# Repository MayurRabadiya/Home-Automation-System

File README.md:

# Home Automation System
## What is Home Automation?
Home automation, often referred to as smart home technology, involves the automation of household activities through various control systems. This includes the monitoring and control of home attributes such as lighting, climate, entertainment systems, and appliances. Additionally, home automation encompasses security features like access control and alarm systems. When connected to the Internet, these devices become integral components of the Internet of Things (IoT).

## Project Aim
The objective of our Smart Module is to provide a comprehensive solution for controlling home electronic appliances using a smartphone, touch control, IR remote, and voice assistants like Alexa and Google Assistant.

## Modes of Operation
1. Touch Control: Utilizes a Cypress capacitive touch sensor to detect user touch inputs and respond based on the previous state of the relay.

2. Voice Command: Voice commands are facilitated through Alexa, which publishes MQTT messages. The ESP8266 module subscribes to these topics to receive the messages. Communication between the Cypress chip and ESP8266 occurs via I2C, enabling the system to react appropriately.

3. IR Remote: The ESP8266 decodes input from an IR remote and sends commands to the Cypress chip via I2C communication. The Cypress chip processes these commands to control the relays.

4. Smartphone: A smartphone app publishes MQTT messages that the ESP8266 module subscribes to. These messages are communicated to the Cypress chip through I2C, enabling the system to control the relays based on the received commands.

This project demonstrates the integration of various modern technologies to create a versatile and user-friendly home automation system.

## Images
Touch pad top side           |  Touch pad bottom side
:-------------------------:|:-------------------------:
  |  

Power base top side           |  Power base bottom side
:-------------------------:|:-------------------------:
  |  

Front Cover      
| :-------------------------:|
|   |

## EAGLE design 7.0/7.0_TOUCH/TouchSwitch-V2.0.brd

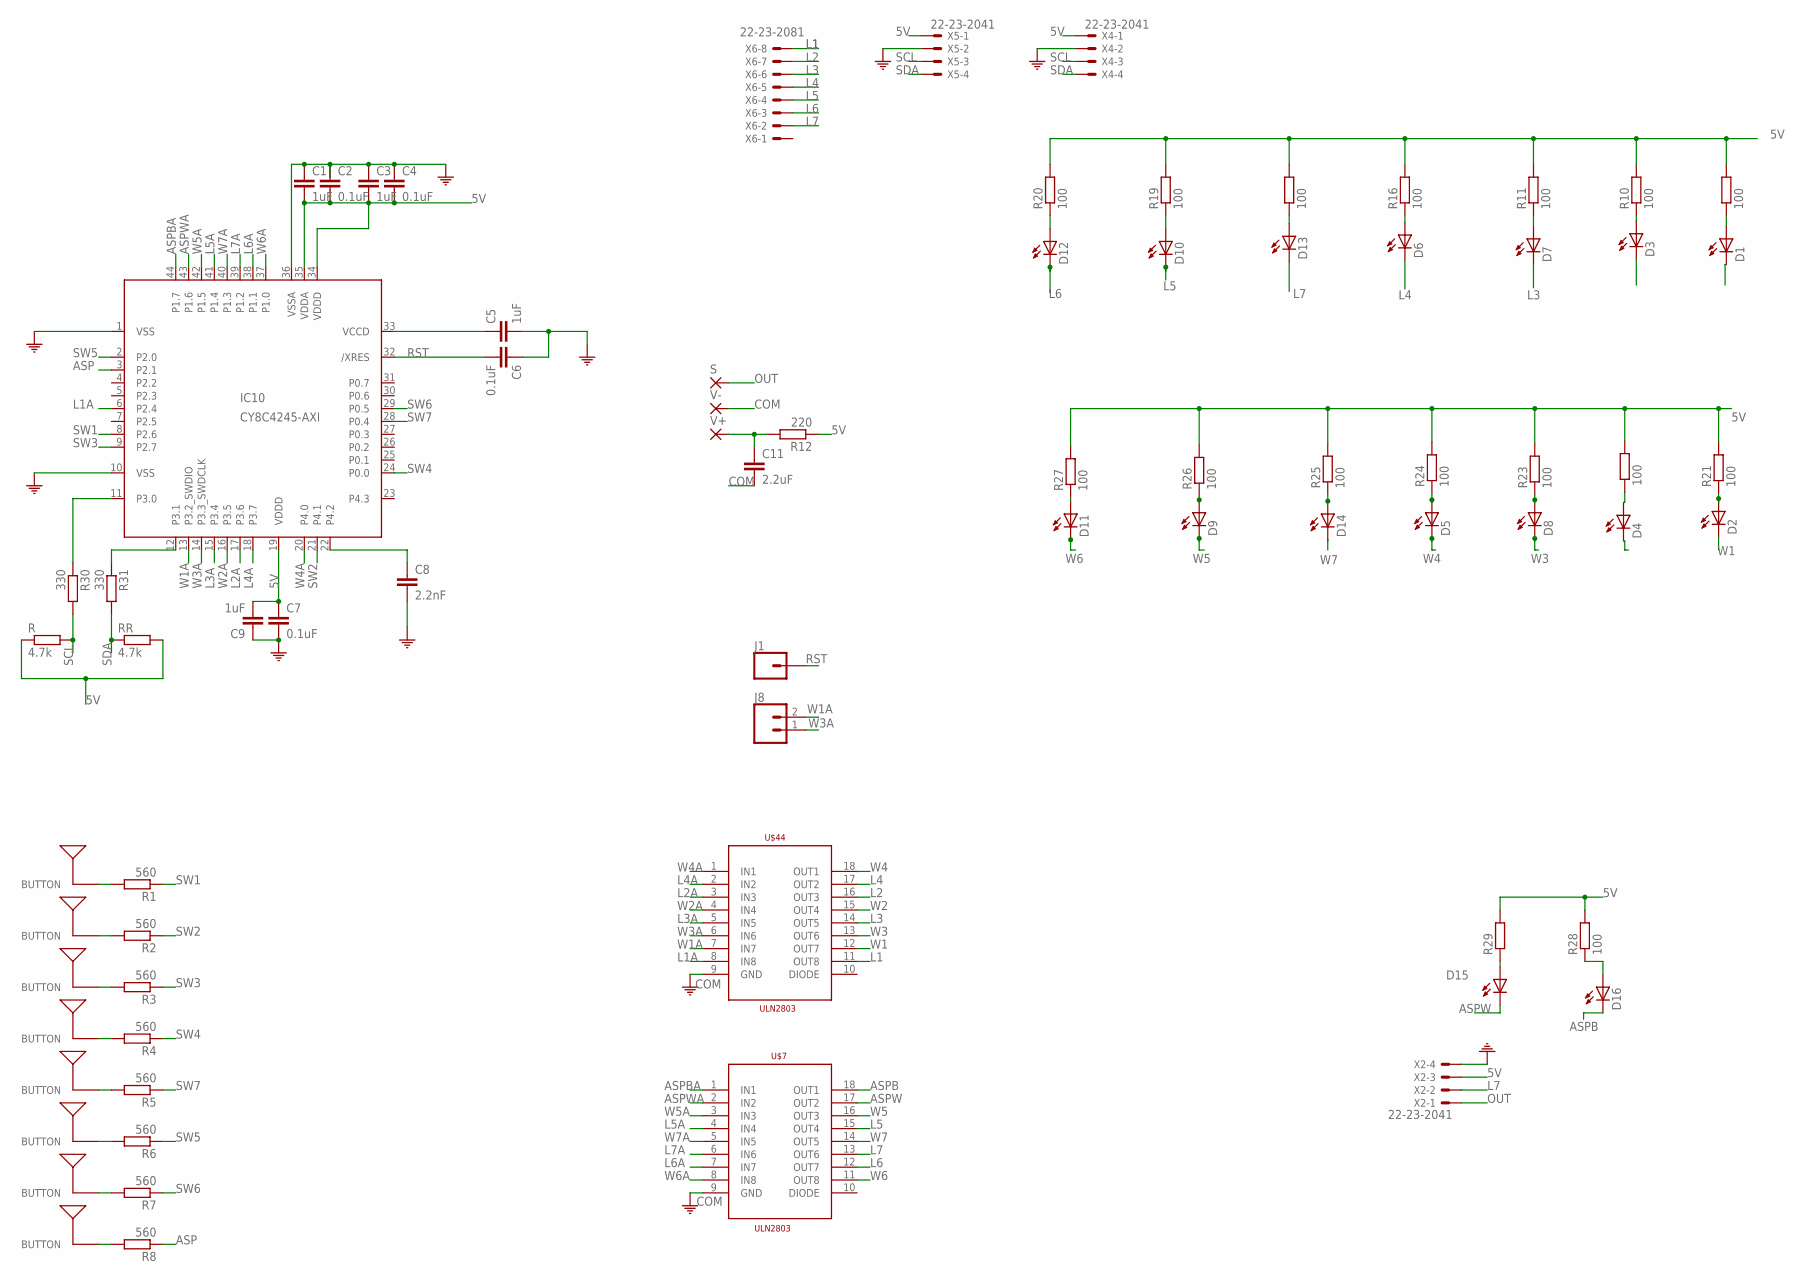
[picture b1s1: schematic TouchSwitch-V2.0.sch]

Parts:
B1, B2, B3, B4, B5, B6, B7, B8: BUTTON_PASSIVE12MM; BUTTON_PASSIVE_12MM
C1, C3, C5, C9: 1uF; C1206
C2, C4, C6, C7: 0.1uF; C1206
C8: 2.2nF; C1206
C11: 2.2uF; C1206
D1, D2, D3, D4, D5, D6, D7, D8, D9, D10, D11, D12, D13, D14, D15, D16: LEDCHIPLED_1206; CHIPLED_1206
IC10: CY8C4245-AXI; 44-TQFP-0.8
J1: CONN_01; 1X01
J8: CONN_02; 1X02
R: 4.7k; R0805
R1, R2, R3, R4, R5, R6, R7, R8: 560; R0805
R9, R10, R11, R16, R18, R19, R20, R21, R22, R23, R24, R25, R26, R27, R28, R29: 100; R0805
R12: 220; R0805
R30, R31: 330; R0805
RR: 4.7k; R0805
S: SMD2; SMD1,27-2,54
U$7, U$44: ULN2803; SO18L
V+: SMD2; SMD1,27-2,54
V-: SMD2; SMD1,27-2,54
X2, X4, X5: 22-23-2041
X6: 22-23-2081

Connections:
5V: C1.2, C2.2, C3.2, C4.2, C7.1, C9.2, IC10.19 (VDDD), IC10.34 (VDDD), IC10.35 (VDDA), R.1, R9.2, R10.2, R11.2, R12.1, R16.2, R18.2, R19.2, R20.2, R21.2, R22.2, R23.2, R24.2, R25.2, R26.2, R27.2, R28.2, R29.2, RR.2, X2.3, X4.1, X5.1
ASP: IC10.3 (P2.1), R8.1
ASPB: D16.C, U$7.18 (OUT1)
ASPBA: IC10.44 (P1.7), U$7.1 (IN1)
ASPW: D15.C, U$7.17 (OUT2)
ASPWA: IC10.43 (P1.6), U$7.2 (IN2)
COM: C1.1, C2.1, C3.1, C4.1, C5.2, C6.1, C7.2, C8.2, C9.1, C11.2, IC10.1 (VSS), IC10.10 (VSS), IC10.36 (VSSA), U$7.9 (GND), U$44.9 (GND), V-.1, X2.4, X4.2, X5.2
L1: D1.C, U$44.11 (OUT8), X6.8
L1A: IC10.6 (P2.4), U$44.8 (IN8)
L2: D3.C, U$44.16 (OUT3), X6.7
L2A: IC10.17 (P3.6), U$44.3 (IN3)
L3: D7.C, U$44.14 (OUT5), X6.6
L3A: IC10.15 (P3.4), U$44.5 (IN5)
L4: D6.C, U$44.17 (OUT2), X6.5
L4A: IC10.18 (P3.7), U$44.2 (IN2)
L5: D10.C, U$7.15 (OUT4), X6.4
L5A: IC10.41 (P1.4), U$7.4 (IN4)
L6: D12.C, U$7.12 (OUT7), X6.3
L6A: IC10.38 (P1.1), U$7.7 (IN7)
L7: D13.C, U$7.13 (OUT6), X2.2, X6.2
L7A: IC10.39 (P1.2), U$7.6 (IN6)
unnamed: C8.1, IC10.22 (P4.2)
unnamed: B8.P$1, R1.2
unnamed: IC10.11 (P3.0), R30.1
unnamed: B1.P$1, R2.2
unnamed: IC10.12 (P3.1), R31.1
unnamed: D10.A, R19.1
unnamed: B2.P$1, R3.2
unnamed: B3.P$1, R4.2
unnamed: B4.P$1, R5.2
unnamed: B5.P$1, R6.2
unnamed: B6.P$1, R7.2
unnamed: D13.A, R18.1
unnamed: C11.1, R12.2, V+.1
unnamed: D12.A, R20.1
unnamed: D6.A, R16.1
unnamed: B7.P$1, R8.2
unnamed: D7.A, R11.1
unnamed: D15.A, R29.1
unnamed: D3.A, R10.1
unnamed: D1.A, R9.1
unnamed: D5.A, R24.1
unnamed: D11.A, R27.1
unnamed: D9.A, R26.1
unnamed: D14.A, R25.1
unnamed: D2.A, R21.1
unnamed: D4.A, R22.1
unnamed: D8.A, R23.1
unnamed: D16.A, R28.1
unnamed: C5.1, IC10.33 (VCCD)
OUT: S.1, X2.1
RST: C6.2, IC10.32 (/XRES), J1.1
SCL: R.2, R30.2, X4.3, X5.3
SDA: R31.2, RR.1, X4.4, X5.4
SW1: IC10.8 (P2.6), R1.1
SW2: IC10.21 (P4.1), R2.1
SW3: IC10.9 (P2.7), R3.1
SW4: IC10.24 (P0.0), R4.1
SW5: IC10.2 (P2.0), R6.1
SW6: IC10.29 (P0.5), R7.1
SW7: IC10.28 (P0.4), R5.1
W1: D2.C, U$44.12 (OUT7)
W1A: IC10.13 (P3.2_SWDIO), J8.2, U$44.7 (IN7)
W2: D4.C, U$44.15 (OUT4)
W2A: IC10.16 (P3.5), U$44.4 (IN4)
W3: D8.C, U$44.13 (OUT6)
W3A: IC10.14 (P3.3_SWDCLK), J8.1, U$44.6 (IN6)
W4: D5.C, U$44.18 (OUT1)
W4A: IC10.20 (P4.0), U$44.1 (IN1)
W5: D9.C, U$7.16 (OUT3)
W5A: IC10.42 (P1.5), U$7.3 (IN3)
W6: D11.C, U$7.11 (OUT8)
W6A: IC10.37 (P1.0), U$7.8 (IN8)
W7: D14.C, U$7.14 (OUT5)
W7A: IC10.40 (P1.3), U$7.5 (IN5)

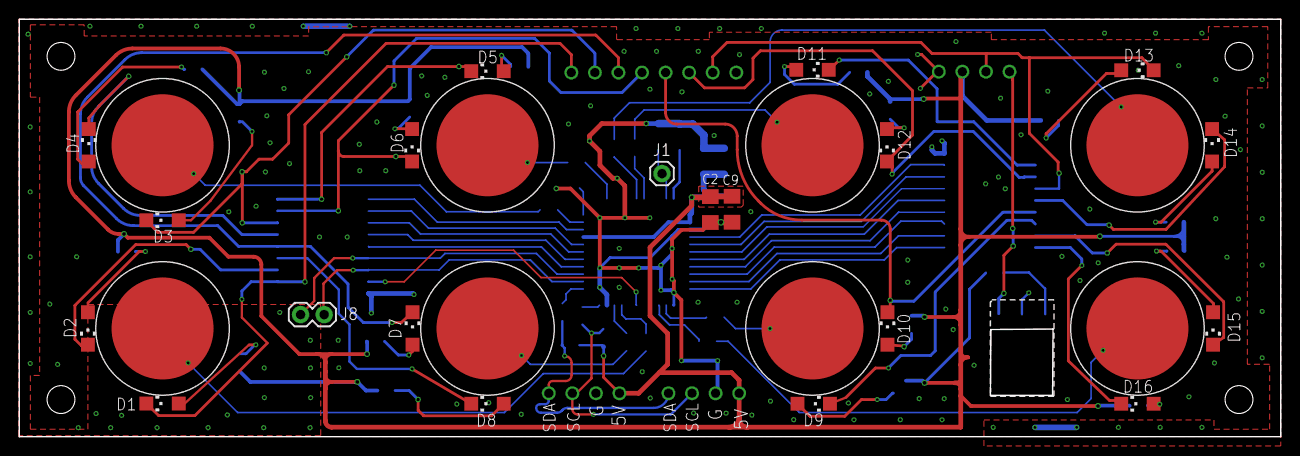
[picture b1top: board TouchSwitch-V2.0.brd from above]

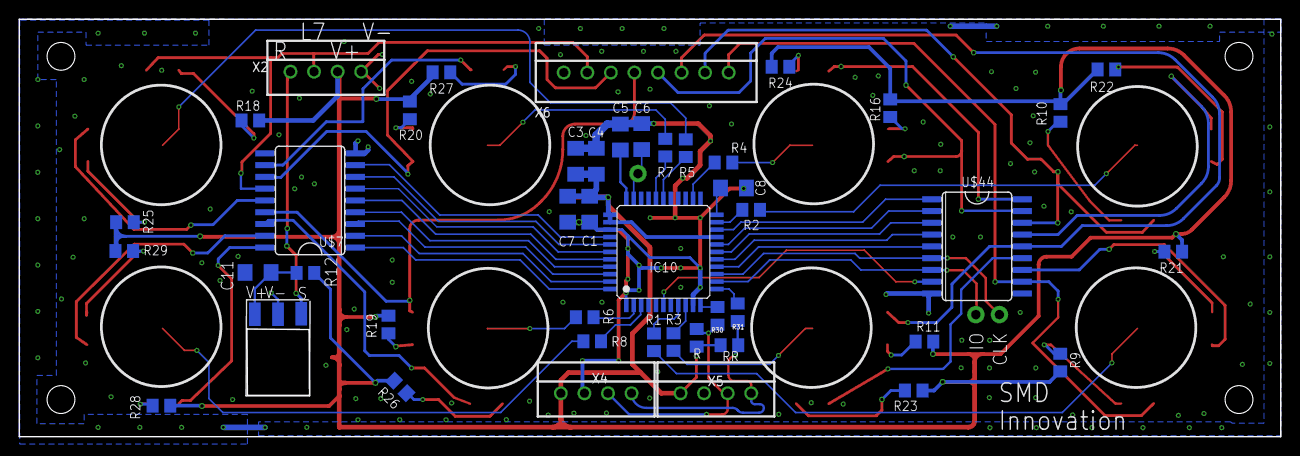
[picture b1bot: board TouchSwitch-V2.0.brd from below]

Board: 2 copper layers, 136.0 x 45.0 mm, 75 parts (47 on the bottom side), 75 nets.

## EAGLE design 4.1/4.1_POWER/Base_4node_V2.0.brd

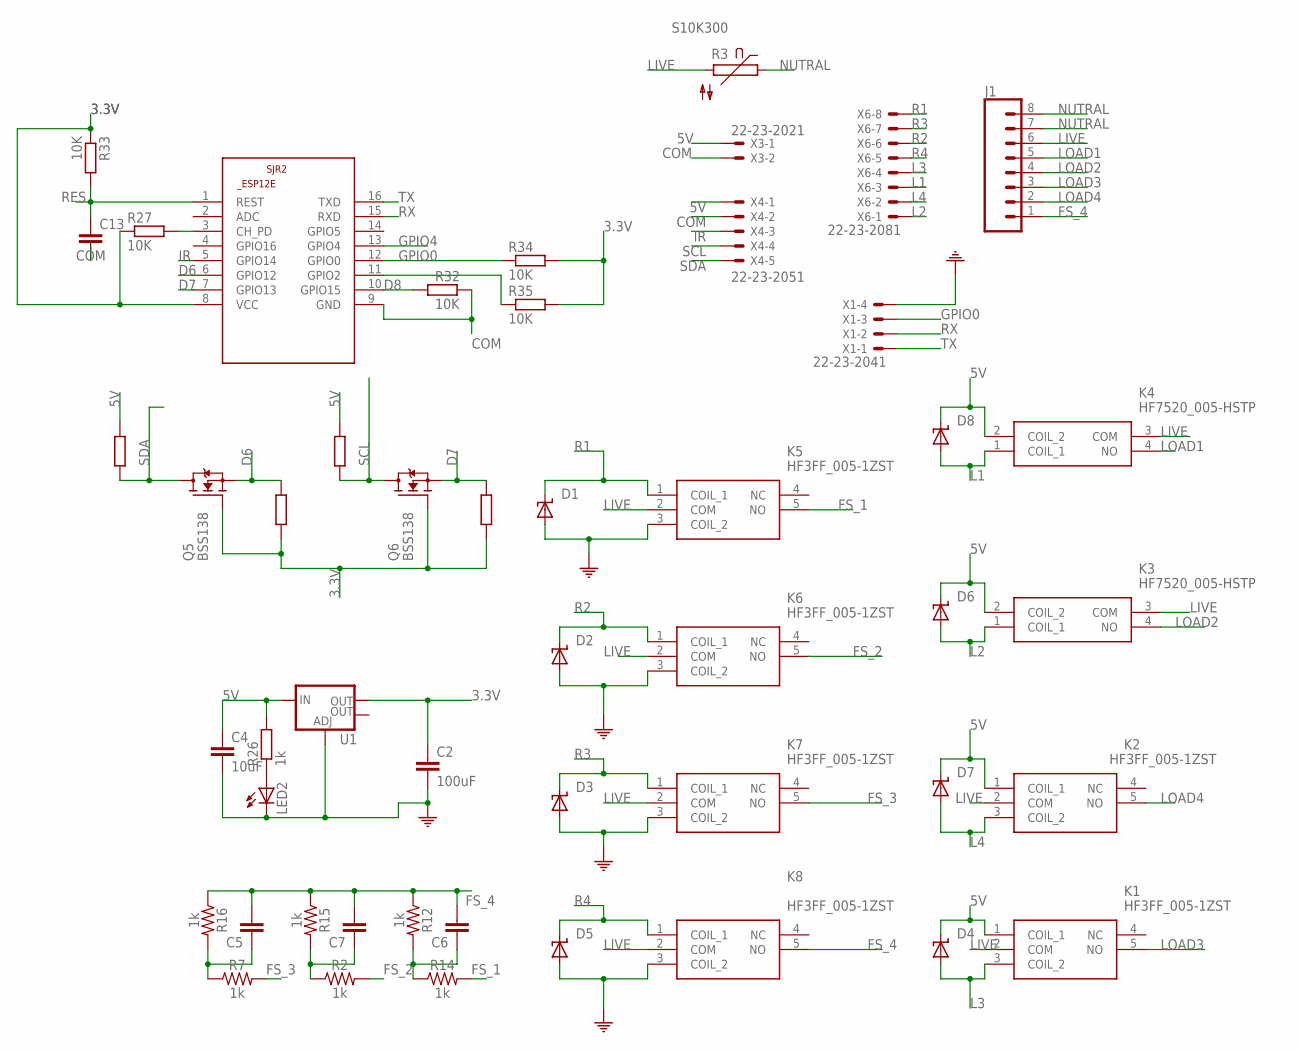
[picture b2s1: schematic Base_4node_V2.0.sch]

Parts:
C2: 100uF; C1206
C4: 10uF; C1206
C5: C-EU275-134X316; C275-134X316
C6: C-EU275-093X316; C275-093X316
C7: C-EU275-113X316; C275-113X316
C13: C-EUC0805; C0805
D1, D2, D3, D4, D5, D6, D7, D8: SUPPRESSOR-SMBJ; SMBJ
J1: CONN_083.5MM-8; SCREWTERMINAL-3.5MM-8
K1, K2, K5, K6, K7, K8: HF3FF_005-1ZST; HF3FF0051ZST
K3, K4: HF7520_005-HSTP; HF7520005HSTP
LED2: LEDCHIPLED_1206; CHIPLED_1206
Q5, Q6: BSS138; SOT23
R2, R7, R14: 1k; AXIAL-0.1
R3: S10K300
R12, R15, R16: 1k; AXIAL-0.3
R26: 1k; R0805
R27, R32, R33, R34, R35, R36, R37, R38, R39: 10K; R0805
SJR2: ESP8266-12EESP12E; ESP8266-ESP12E
U1: V_REG_LM1117SOT223; SOT223
X1: 22-23-2041
X3: 22-23-2021
X4: 22-23-2051
X6: 22-23-2081

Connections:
3.3V: C2.1, Q5.1 (G), Q6.1 (G), R27.1, R33.1, R34.2, R35.2, R37.2, R39.2, SJR2.8 (VCC), U1.2 (OUT)
5V: C4.1, D4.C, D6.C, D7.C, D8.C, K1.1 (COIL_1), K2.1 (COIL_1), K3.2 (COIL_2), K4.2 (COIL_2), R26.2, R36.2, R38.2, U1.3 (IN), X3.1, X4.1
COM: C2.2, C4.2, C13.2, D1.A, D2.A, D3.A, D5.A, K5.3 (COIL_2), K6.3 (COIL_2), K7.3 (COIL_2), K8.3 (COIL_2), LED2.C, R32.2, SJR2.9 (GND), U1.1 (ADJ), X1.4, X3.2, X4.2
D6: Q5.2 (S), R37.1, SJR2.6 (GPIO12)
D7: Q6.2 (S), R39.1, SJR2.7 (GPIO13)
D8: R32.1, SJR2.10 (GPIO15)
FS_1: K5.5 (NO), R14.P$2 (2)
FS_2: K6.5 (NO), R2.P$2 (2)
FS_3: K7.5 (NO), R7.P$2 (2)
FS_4: C5.2, C6.2, C7.2, J1.1, K8.5 (NO), R12.P$1 (1), R15.P$1 (1), R16.P$1 (1)
GPIO0: R34.1, SJR2.12 (GPIO0), X1.3
GPIO4: SJR2.13 (GPIO4)
IR: SJR2.5 (GPIO14), X4.3
L1: D8.A, K4.1 (COIL_1), X6.3
L2: D6.A, K3.1 (COIL_1), X6.1
L3: D4.A, K1.3 (COIL_2), X6.4
L4: D7.A, K2.3 (COIL_2), X6.2
LIVE: J1.6, K1.2 (COM), K2.2 (COM), K3.3 (COM), K4.3 (COM), K5.2 (COM), K6.2 (COM), K7.2 (COM), K8.2 (COM), R3.2
LOAD1: J1.5, K4.4 (NO)
LOAD2: J1.4, K3.4 (NO)
LOAD3: J1.3, K1.5 (NO)
LOAD4: J1.2, K2.5 (NO)
unnamed: C6.1, R12.P$2 (2), R14.P$1 (1)
unnamed: C7.1, R2.P$1 (1), R15.P$2 (2)
unnamed: C5.1, R7.P$1 (1), R16.P$2 (2)
unnamed: LED2.A, R26.1
unnamed: R35.1, SJR2.11 (GPIO2)
unnamed: R27.2, SJR2.3 (CH_PD)
NUTRAL: J1.7, J1.8, R3.1
R1: D1.C, K5.1 (COIL_1), X6.8
R2: D2.C, K6.1 (COIL_1), X6.6
R3: D3.C, K7.1 (COIL_1), X6.7
R4: D5.C, K8.1 (COIL_1), X6.5
RES: C13.1, R33.2, SJR2.1 (REST)
RX: SJR2.15 (RXD), X1.2
SCL: Q6.3 (D), R36.1, X4.4
SDA: Q5.3 (D), R38.1, X4.5
TX: SJR2.16 (TXD), X1.1

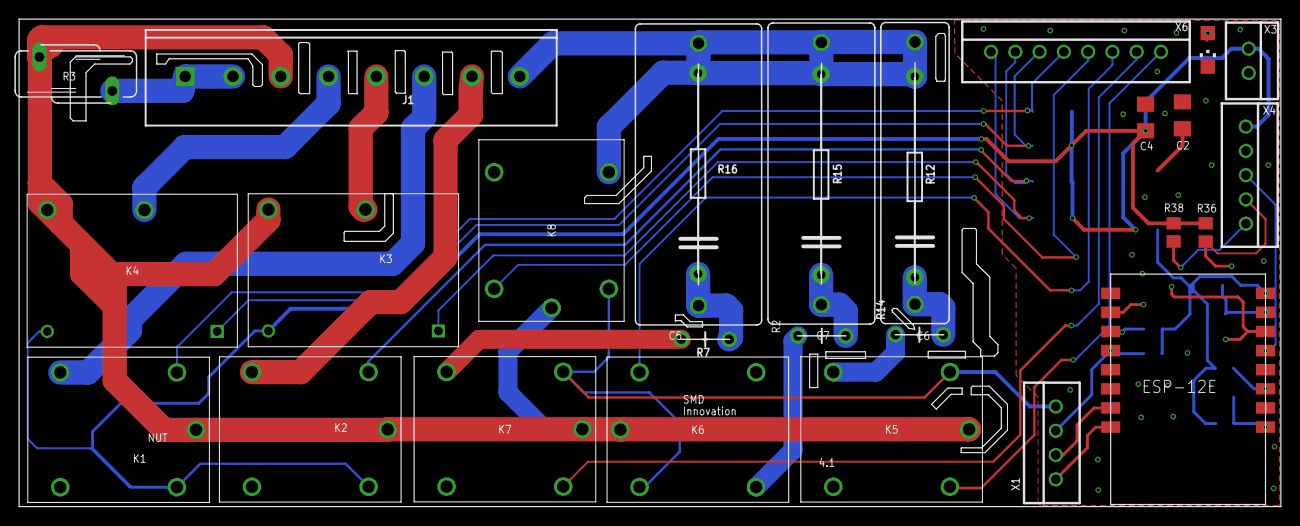
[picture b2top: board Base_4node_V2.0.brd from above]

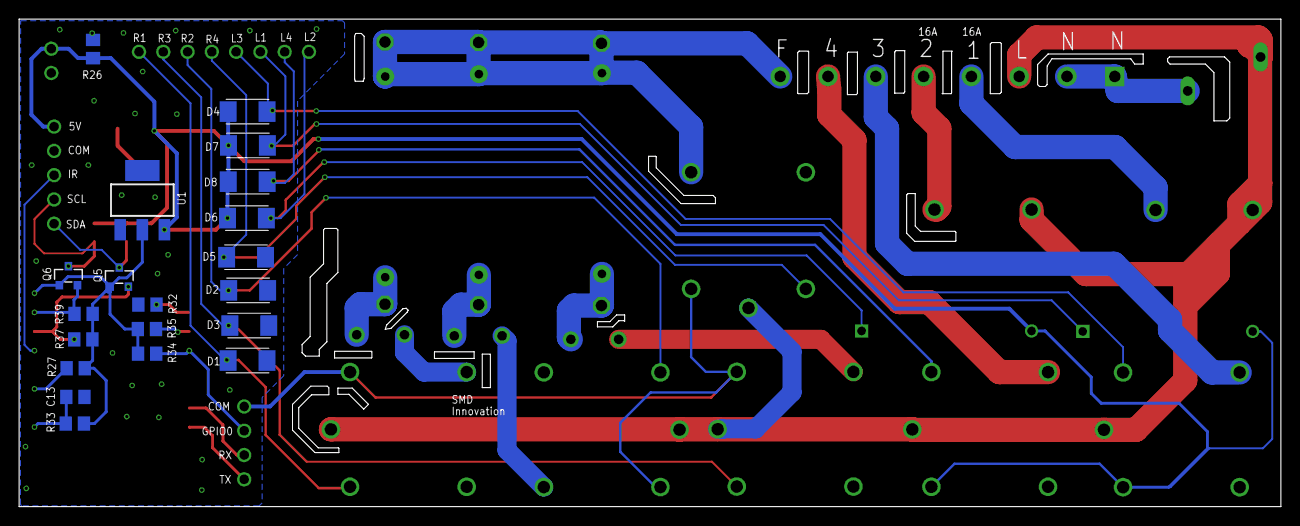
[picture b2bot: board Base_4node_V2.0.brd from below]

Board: 2 copper layers, 131.9 x 50.9 mm, 49 parts (20 on the bottom side), 37 nets.

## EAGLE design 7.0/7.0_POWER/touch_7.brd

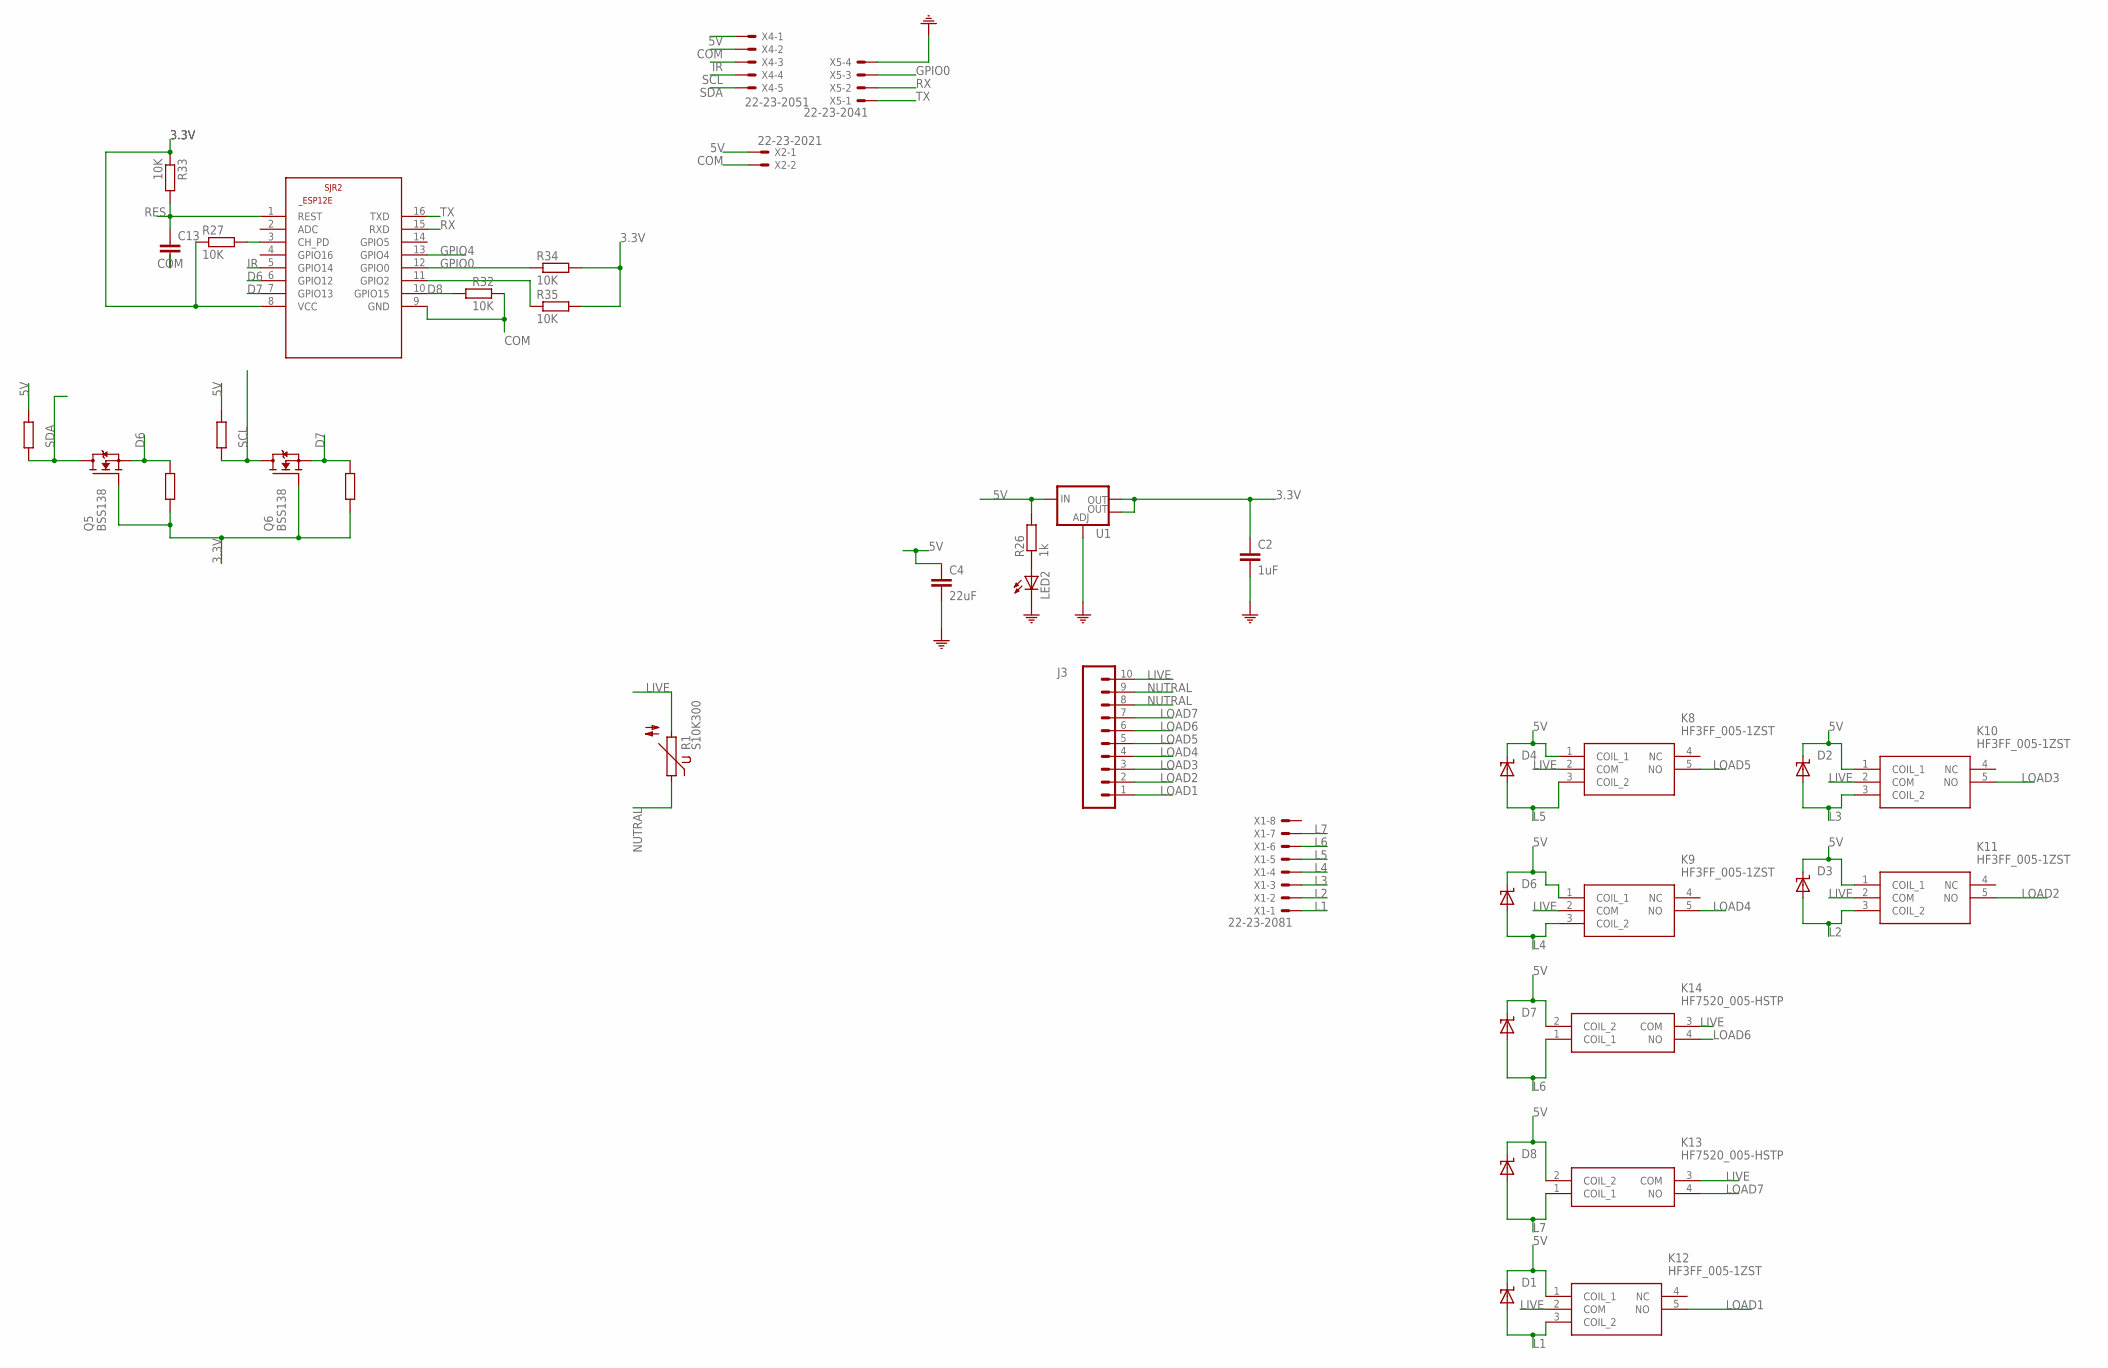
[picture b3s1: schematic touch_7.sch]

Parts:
C2: 1uF; C1206
C4: 22uF; C1206
C13: C-EUC0805; C0805
D1, D2, D3, D4, D6, D7, D8: SUPPRESSOR-SMBJ; SMBJ
J3: CONN_083.5MM-8; SCREWTERMINAL-3.5MM-8
K8, K9, K10, K11, K12: HF3FF_005-1ZST; HF3FF0051ZST
K13, K14: HF7520_005-HSTP; HF7520005HSTP
LED2: LEDCHIPLED_1206; CHIPLED_1206
Q5, Q6: BSS138; SOT23
R1: S10K300
R26: 1k; R0805
R27, R32, R33, R34, R35, R36, R37, R38, R39: 10K; R0805
SJR2: ESP8266-12EESP12E; ESP8266-ESP12E
U1: V_REG_LM1117SOT223; SOT223
X1: 22-23-2081
X2: 22-23-2021
X4: 22-23-2051
X5: 22-23-2041

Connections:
3.3V: C2.1, Q5.1 (G), Q6.1 (G), R27.1, R33.1, R34.2, R35.2, R37.2, R39.2, SJR2.8 (VCC), U1.2 (OUT), U1.4 (OUT)
5V: C4.1, D1.C, D2.C, D3.C, D4.C, D6.C, D7.C, D8.C, K8.1 (COIL_1), K9.1 (COIL_1), K10.1 (COIL_1), K11.1 (COIL_1), K12.1 (COIL_1), K13.2 (COIL_2), K14.2 (COIL_2), R26.2, R36.2, R38.2, U1.3 (IN), X2.1, X4.1
COM: C2.2, C4.2, C13.2, LED2.C, R32.2, SJR2.9 (GND), U1.1 (ADJ), X2.2, X4.2, X5.4
D6: Q5.2 (S), R37.1, SJR2.6 (GPIO12)
D7: Q6.2 (S), R39.1, SJR2.7 (GPIO13)
D8: R32.1, SJR2.10 (GPIO15)
GPIO0: R34.1, SJR2.12 (GPIO0), X5.3
GPIO4: SJR2.13 (GPIO4)
IR: SJR2.5 (GPIO14), X4.3
L1: D1.A, K12.3 (COIL_2), X1.1
L2: D3.A, K11.3 (COIL_2), X1.2
L3: D2.A, K10.3 (COIL_2), X1.3
L4: D6.A, K9.3 (COIL_2), X1.4
L5: D4.A, K8.3 (COIL_2), X1.5
L6: D7.A, K14.1 (COIL_1), X1.6
L7: D8.A, K13.1 (COIL_1), X1.7
LIVE: J3.10, K8.2 (COM), K9.2 (COM), K10.2 (COM), K11.2 (COM), K12.2 (COM), K13.3 (COM), K14.3 (COM), R1.2
LOAD1: J3.1, K12.5 (NO)
LOAD2: J3.2, K11.5 (NO)
LOAD3: J3.3, K10.5 (NO)
LOAD4: J3.4, K9.5 (NO)
LOAD5: J3.5, K8.5 (NO)
LOAD6: J3.6, K14.4 (NO)
LOAD7: J3.7, K13.4 (NO)
unnamed: LED2.A, R26.1
unnamed: R35.1, SJR2.11 (GPIO2)
unnamed: R27.2, SJR2.3 (CH_PD)
NUTRAL: J3.8, J3.9, R1.1
RES: C13.1, R33.2, SJR2.1 (REST)
RX: SJR2.15 (RXD), X5.2
SCL: Q6.3 (D), R36.1, X4.4
SDA: Q5.3 (D), R38.1, X4.5
TX: SJR2.16 (TXD), X5.1

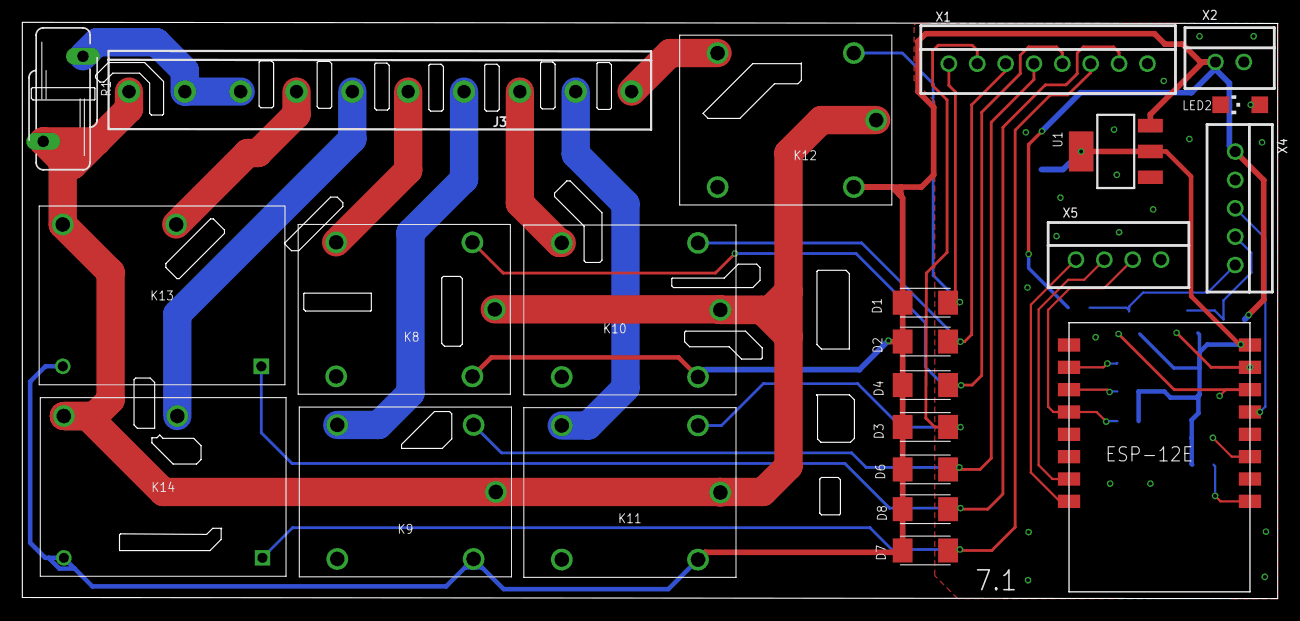
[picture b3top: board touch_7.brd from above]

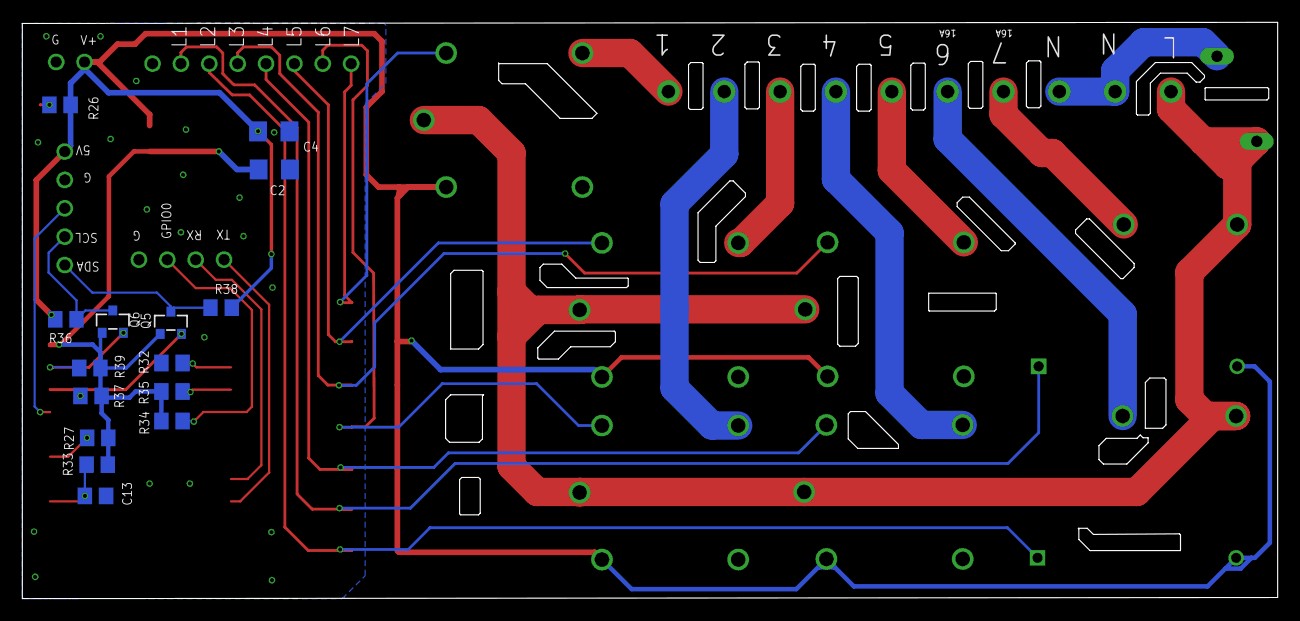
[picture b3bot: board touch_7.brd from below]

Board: 2 copper layers, 112.3 x 51.5 mm, 38 parts (15 on the bottom side), 32 nets.

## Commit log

2024-07-15 Files
2024-07-16 pictures

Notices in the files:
parts and their libraries:
SparkFun-IC-Power: Licensing: Creative Commons ShareAlike 4.0 International - https://creativecommons.org/licenses/by-sa/4.0
touch_pad_: License : http://creativecommons.org/licenses/by-sa/4.0/ (Creative Commons 4.0)
